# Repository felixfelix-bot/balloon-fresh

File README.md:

# Pico-Balloon Tracker & E80 Range Test Bench

Ultralight (<15 g) pico-balloon tracker (ESP32-C3 + Semtech LR2021) with a
dedicated **E80-STM32 bench firmware** for distributed LoRa/FLRC range
testing.  Two boards, two laptops, one `make` command each — that's all
it takes to run a full PER / RSSI / SNR sweep.

---

## ⚡ Getting Started

```bash
git clone https://github.com/felixfelix-bot/balloon-fresh.git
cd balloon-fresh/firmware/e80-stm32-bench
git checkout feat/2g4-sweep

# One-time: flash the board (needs both USB cables connected)
make flash

# On the TX machine:
make tx

# On the RX machine (within 4 minutes of `make tx`):
make rx

# After both finish, merge logs:
make range-merge RX=rx-log.csv TX=tx-log.csv
```

**That's it.** The system auto-detects serial ports, computes a synchronised
start time (T0), beeps a countdown, and writes results to CSV.

> **Want the minimal package?** Download the pre-built
> [range-test ZIP](../../releases) — contains only the files you need to
> flash + run TX/RX. See [Part 4](#4-minimal-range-test-zip) below.

---

## 📋 Table of Contents

| # | Section |
|---|---------|
| 1 | [What is this repo?](#1-what-is-this-repo) |
| 2 | [Hardware Requirements](#2-hardware-requirements) |
| 3 | [Quick Start (Linux / macOS / Windows)](#3-quick-start) |
| 4 | [Minimal Range-Test ZIP](#4-minimal-range-test-zip) |
| 5 | [Repository Structure](#5-repository-structure) |
| 6 | [Key Documentation](#6-key-documentation) |
| 7 | [Tools Reference](#7-tools-reference) |
| 8 | [Config Presets](#8-config-presets) |
| 9 | [Development & Testing](#9-development--testing) |
| 10 | [Hardware](#10-hardware) |

---

## 1. What is this repo?

This repository hosts **two related projects**:

1. **Pico-Balloon Tracker** — An ESP32-C3 + Semtech LR2021 ultra-light
   balloon tracker (<15 g) with multi-band LoRa (2.4 GHz + Sub-GHz), FLRC
   high-speed mode, 3D PCB-Yagi antenna array, solar/supercap power, and
   BMP280 sensing.

2. **E80 Range Test Bench** — A STM32F103C8T6 based firmware (`firmware/e80-stm32-bench/`)
   for the E80-900MBL-02 board, used for distributed LoRa/FLRC range
   testing.  Measures PER, RSSI, SNR, and bit error rate across modulation
   schemes at various distances.  Two boards act as TX/RX, each connected
   to a separate computer.  Role is set at runtime — boards are
   interchangeable.

---

## 2. Hardware Requirements

| Item | Qty | Notes |
|------|-----|-------|
| E80-900MBL-02 board | 2 | One per machine. Boards are interchangeable (TX/RX is software-selected). |
| Computer (laptop/mini PC) | 2 | One per board. Linux, macOS, or Windows. |
| USB cables | 2 per board | CH340 USB-serial (data) + CMSIS-DAP/Pico SWD probe (debug). Both required. |
| Phone with GPS | 1 (opt.) | For distance measurement. Any app that exports GPX/KML. |

### E80 Board Anatomy

- **STM32F103C8** — microcontroller (64 KB flash / 20 KB RAM)
- **LR2021** — Semtech LoRa Gen 4 radio (supports LoRa + FLRC)
- **CH340** — USB-serial chip for host communication
- **Raspberry Pi Pico** (CMSIS-DAP) — SWD probe for flashing + board reset

### Pico-Balloon Hardware

| Component | Spec |
|-----------|------|
| MCU | ESP32-C3 (ESP-C3-12F / XIAO ESP32C3) |
| LoRa | Semtech LR2021 (Gen 4) / LR1121 (Gen 3 alt.) |
| PA/LNA | Skyworks SKY66112-11 (+22 dBm TX, +14 dB LNA RX) |
| Antennas | 4× PCB-Yagi + SP4T switch (lighthouse mode) |
| Power | 12× solar cells → BAT54 → 2× 3.3 F supercaps → TPS7A02 LDO |
| Sensor | BMP280 (pressure/temperature) |
| Target weight | <15 g |

---

## 3. Quick Start

### Linux

```bash
# Install toolchain
sudo apt install cmake arm-none-eabi-gcc openocd python3 python3-pip
pip install pyserial

# Clone & build
git clone https://github.com/felixfelix-bot/balloon-fresh.git
cd balloon-fresh/firmware/e80-stm32-bench
git checkout feat/2g4-sweep

# Add user to dialout group (needed for serial port access)
sudo usermod -aG dialout "$USER"
# Log out and back in, or: newgrp dialout

# Flash firmware (first time only — both USB cables connected)
make flash
```

### macOS

```bash
# Install toolchain
brew install cmake gcc-arm-embedded openocd python3
pip3 install pyserial

# Clone & build
git clone https://github.com/felixfelix-bot/balloon-fresh.git
cd balloon-fresh/firmware/e80-stm32-bench
git checkout feat/2g4-sweep

make flash
```

### Windows

1. Install [STM32CubeIDE](https://www.st.com/en/development-tools/stm32cubeide.html)
   or a standalone `arm-none-eabi-gcc` toolchain.
2. Install [OpenOCD](https://gnutoolchains.com/arm-eabi/openocd/).
3. Install [Python 3](https://www.python.org/downloads/) + `pip install pyserial`.
4. Clone the repo, open a terminal (Git Bash or PowerShell) in
   `firmware/e80-stm32-bench/`.
5. Run `make flash`.

### Running a Test

```bash
# On TX machine:
make tx

# On RX machine (within 4 minutes of make tx):
make rx

# After both finish (either machine):
make range-merge RX=rx-log.csv TX=tx-log.csv
```

> For full instructions including flashing details, serial port detection,
> GPS stitching, and troubleshooting, see the
> **[E80 Range Test Operator Guide](firmware/e80-stm32-bench/docs/RANGE-TEST-GUIDE.md)**.

---

## 4. Minimal Range-Test ZIP

For operators who just want the files needed to flash + run TX/RX without
cloning the whole repo:

**Download:** See [GitHub Releases](../../releases) for `e80-range-test-*.zip`.

**Build your own:**

```bash
cd firmware/e80-stm32-bench
bash tools/create-range-test-zip.sh
# Output: e80-range-test-<sha7>.zip
```

The ZIP contains:

| Path | Description |
|------|-------------|
| `Makefile` | Convenience targets (flash, tx, rx, merge) |
| `CMakeLists.txt` | Firmware build config |
| `cmake/` | Toolchain file (arm-none-eabi) |
| `ld/` | Linker scripts (STM32F103C8) |
| `src/` | Firmware source code |
| `third_party/` | STM32 HAL + Semtech LR2021 driver |
| `tools/e80_bench_ctl.py` | Board controller — TX/RX, PER bench |
| `tools/e80_detect.py` | Auto-detect board serial port |
| `tools/gps_stitch.py` | Stitch GPS track onto RX packet log |
| `tools/merge_csvs.py` | Merge TX + RX logs into PER report |
| `tools/countdown.py` | Countdown timer with beeps |
| `configs/envelope-4cfg-max.json` | Default range test preset (4 configs, max payload) |
| `configs/outdoor-10.json` | Outdoor range test preset (10 pkts per config) |
| `docs/RANGE-TEST-GUIDE.md` | Full operator guide |
| `README-RANGE-TEST.txt` | Quick start card |

---

## 5. Repository Structure

```
balloon-fresh/
├── firmware/
│   ├── e80-stm32-bench/          # E80 STM32 range test firmware
│   │   ├── Makefile              # Flash, tx, rx, merge targets
│   │   ├── CMakeLists.txt        # Firmware build config
│   │   ├── src/                  # Firmware source (bench, radio, console)
│   │   ├── tools/                # Python tools (comms, GPS, CSV, sweep)
│   │   ├── cmake/                # ARM cross-compile toolchain
│   │   ├── ld/                   # STM32 linker scripts
│   │   ├── third_party/          # STM32 HAL + Semtech LR2021 driver
│   │   ├── docs/                 # RANGE-TEST-GUIDE, flashing, timing analysis
│   │   ├── tests/                # Host-side unit tests (C unit + pytest)
│   │   └── FLASHING.md           # Flashing procedures
│   ├── esp32-c3-flrc/            # ESP32-C3 FLRC bench firmware
│   ├── esp32-bootsel-controller/ # ESP32 boot/select controller
│   ├── esp32-uart-bridge/        # UART bridge firmware
│   ├── rp2040-flrc-max/          # RP2040 FLRC tests
│   └── scripts/                  # Build/deploy scripts
├── mesh-stack/                   # ESP-NOW mesh + FLRC bench + LR2021 drivers
├── hardware/                     # PCB design (KiCad), enclosures
├── configs/                      # Range test config presets (JSON)
├── tools/                        # Shared repo-wide tools & scripts
├── docs/                         # Project documentation, ADRs, plans
├── data/                         # Captured test data & analysis
├── tests/                        # Integration tests
├── bom/                          # Bill of materials
├── ansible/                      # Deployment playbooks (range-setup)
├── scripts/                      # Repo-wide automation scripts
└── tracker/                      # Ground station & tracker firmware
```

---

## 6. Key Documentation

| Document | Description |
|----------|-------------|
| **[Harmonized Cross-Board Bench Package](docs/HARMONIZED-BENCH-PACKAGE.md)** | Entry point for cross-board (E80 / ESP32 / RP2040) bench work — real repo URLs and branches, build/flash per family, running a session, handing data back |
| [Harmonized Results](docs/HARMONIZED-RESULTS.md) | Results summary by board-pair × band × LEN × BR, with raw CSV links; 868 MHz baseline vs 2.4 GHz semantics |
| [Harmonized Run Report Template](docs/HARMONIZED-RUN-REPORT-TEMPLATE.md) | Fill-in template for one harmonized run (identity, provenance, matrix, acceptance, results, anomalies) |
| [Bench Console Spec](docs/BENCH-CONSOLE-SPEC.md) | Normative cross-board console protocol (`ID?/SET/N/PKT/STAT?`, framing, bands) |
| **[E80 Range Test Guide](firmware/e80-stm32-bench/docs/RANGE-TEST-GUIDE.md)** | Complete self-contained operator guide — hardware setup, flashing, TX/RX, merge, GPS, troubleshooting |
| [E80 Flashing Guide](firmware/e80-stm32-bench/FLASHING.md) | Detailed flashing procedures (SWD, stm32flash) |
| [Timing Tolerance Analysis](firmware/e80-stm32-bench/docs/timing-tolerance-analysis.md) | T0 sync mechanism analysis |
| [Hardware Integration Findings](firmware/e80-stm32-bench/docs/hardware-integration-findings.md) | Live hardware test results |
| [Operator Quickstart](firmware/e80-stm32-bench/tools/OPERATOR-QUICKSTART.md) | Quick reference for command structure |
| [ADR Index](docs/adr/) | Architecture Decision Records |
| [Hardware Connections](HARDWARE_CONNECTIONS.md) | Board wiring reference |

---

## 7. Tools Reference

| Tool | Location | Purpose |
|------|----------|---------|
| `e80_bench_ctl.py` | `firmware/e80-stm32-bench/tools/` | Main board controller — TX burst, RX arm, PER measurement, sweep runner |
| `e80_detect.py` | `firmware/e80-stm32-bench/tools/` | Auto-detect E80 board role + serial port (handles CH340 port swapping) |
| `gps_stitch.py` | `firmware/e80-stm32-bench/tools/` | Stitch GPS track points onto RX packet log by nearest timestamp |
| `merge_csvs.py` | `firmware/e80-stm32-bench/tools/` | Merge TX + RX logs into PER report (joins on session/config/pkt_idx) |
| `countdown.py` | `firmware/e80-stm32-bench/tools/` | Countdown to T0 with terminal bell beeps |
| `e80_sweep_full.py` | `firmware/e80-stm32-bench/tools/` | Full modulation sweep (FLRC + LoRa at multiple bitrates/SF) |
| `create-range-test-zip.sh` | `firmware/e80-stm32-bench/tools/` | Build minimal ZIP package for range test operators |

---

## 8. Config Presets

Config files live in `configs/` at the repo root:

| File | Description |
|------|-------------|
| `outdoor-10.json` | Outdoor range test — 10 pkts per config, 868 MHz EU SRD |
| `indoor-baseline.json` | Indoor baseline test |

Each JSON config specifies a list of modulation configurations:

```json
{
  "label": "FLRC-650 LEN64",
  "mod": "flrc",
  "br": 650,
  "pa": 10,
  "freq": 868000000,
  "plen": 64,
  "gap": 5000,
  "n_pkts": 10
}
```

Fields: `mod` (flrc/lora), `sf` (LoRa spreading factor), `bw` (bandwidth kHz),
`br` (bitrate kbps), `pa` (TX power dBm), `freq` (Hz), `plen` (payload bytes),
`gap` (inter-packet gap ms), `n_pkts` (packets per config).

---

## 9. Development & Testing

```bash
# Firmware build
cd firmware/e80-stm32-bench
make firmware          # Cross-compile with arm-none-eabi-gcc

# Host unit tests (uses system gcc)
make test-host

# Run pytest suite
cd firmware/e80-stm32-bench/tools
python3 -m pytest ../tests/ -v

# Run a dry-run of the range test (prints schedule, no hardware)
make range-dry-run
```

---

## 10. Hardware

| Directory | Description |
|-----------|-------------|
| `hardware/` | PCB design files (KiCad), enclosure CAD |
| `bom/` | Bill of materials |
| `docs/pcb/` | PCB design documentation |
| `docs/hardware-reference/` | Hardware reference materials |

---

## License

See individual source files and `firmware/e80-stm32-bench/third_party/`
for licensing details. Third-party drivers retain their original licenses
(Semtech BSD, ST BSD-3-Clause).

## Cross-Board Bench — dieser Branch (`range-tests`)
Dieser Branch ist die Range-Test-Spur der harmonisierten Cross-Board-Messungen
(E80 STM32+LR2021 / ESP32-C3+LR2021 / RP2040+LR2021). Einstiegspunkt für alles
Weitere ist `docs/HARMONIZED-BENCH-PACKAGE.md` im Branch **`main`** desselben
Repos (`https://github.com/felixfelix-bot/balloon-fresh.git`).
> **Wichtig — die Bench-Console liegt NICHT auf diesem Branch.**
> `tools/balloon_sweep.py` und `docs/BENCH-CONSOLE-SPEC.md` gibt es nur auf
> `main` (HARM-Kette, `harm/t5-bench-console`). Auf `range-tests` schlägt
> `ls tools/balloon_sweep.py` fehl. Wer die harmonisierte Console fahren will,
> muss `main` auschecken oder diesen Branch damit mergen; die untenstehenden
> Kommandos sind die *Legacy*-Sweep-Werkzeuge dieses Branches.
### RP2040-Firmware bauen/flashen (dieser Branch)
cd firmware/rp2040
make build-tx        # bzw. build-rx / build-both
make flash-tx        # bzw. flash-rx / flash-both
make monitor-tx      # bzw. monitor-rx
make ports           # Ports neu ermitteln (nicht raten)
### Sweep fahren (Legacy-Weg dieses Branches)
# Board-Mutex ist Pflicht — niemals ohne Lock flashen
BALLOON_TRACK=range-tests python3 ~/repos/balloon-fresh/tools/balloon-board-lock.py \
    acquire board-a --purpose "range sweep" --timeout 120
python3 tools/sweep_flash.py          # flashen
python3 tools/sweep_capture.py 480    # 480 s erfassen (>= 2 Zyklen)
python3 tools/capture_sweep.py        # alternativ: Sweep-Capture
BALLOON_TRACK=range-tests python3 ~/repos/balloon-fresh/tools/balloon-board-lock.py release board-a
Die Ergebnisse und die bekannten Fallstricke dieses Ansatzes (Timing-Drift
zwischen zwei freilaufenden RP2040, Slot-Weiten, IRQ-/RSSI-Opcode-Bugs) stehen in
`docs/SWEEP-RESULTS.md`. Datenübergabe-Konvention dieses Branches:
`docs/data-handover/DATA-HANDOVER-2026-08-17.md`.
### Harmonisierte Session (nur auf `main`)
git checkout main     # Console liegt dort
python3 tools/balloon_sweep.py --tx rp2040 --rx esp32 --session <yymmddHHMM> --dry-run
`REFUSED (pre-hardware, spec enforcement): …` heisst: der Plan verletzt die Spec
(LEN-Cap 255/511, GAP >= 40 000 us bei LEN > 256, Frequenz-Paar). Plan
korrigieren, nicht umgehen. 2.4-GHz-Cross-Board ist nur RP2040<->ESP32 erlaubt.

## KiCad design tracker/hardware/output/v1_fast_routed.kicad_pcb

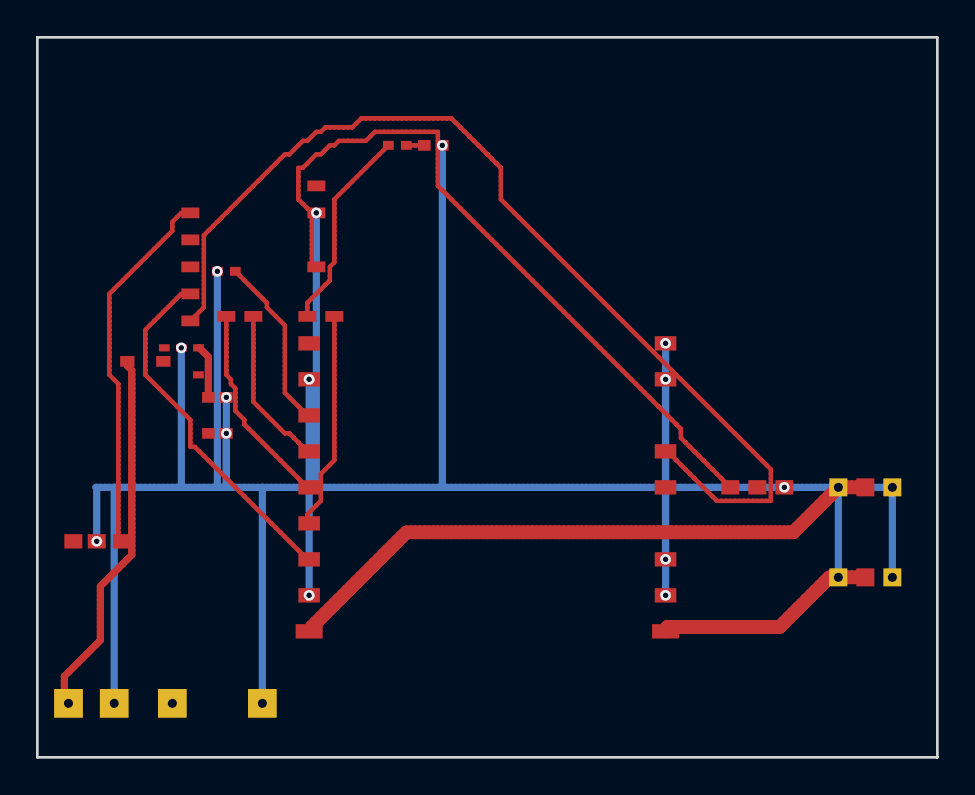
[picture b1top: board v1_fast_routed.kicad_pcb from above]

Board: 2 copper layers, 50.0 x 40.0 mm, 15 parts (0 on the bottom side), 17 nets.

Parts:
ANT1: U.FL-868
ANT2: U.FL-2400
C1, C2: 10uF
C_CAP: Supercap
D1: BAT54
FEM: FEM
LED1: LED-0603
R_LED: 330R
R_PD: 10k
SOLAR: Solar-Conn
U1: ESP32-C3
U2: LR2021F33
U3: MAX-M10S
U4: TPS7A02

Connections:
3V3: C2.1, FEM.VCC, U1.VCC, U2.1, U3.1, U4.4
FEM_TX: FEM.TX, U1.GPIO19
GND: ANT1.2, ANT1.3, ANT2.2, ANT2.3, C1.2, C2.2, C_CAP.2, FEM.GND, LED1.K, R_PD.1, SOLAR.2, U1.GND, U2.2, U2.8, U2.10, U2.11, U2.16, U2.17, U3.2, U4.2
GPS_RX: U1.GPIO1, U3.3
LED_ANODE: LED1.A, R_LED.2
LR2021_BUSY: U1.GPIO4, U2.7
LR2021_DIO9: U1.GPIO5, U2.13
LR2021_RST: U1.GPIO3, U2.14
RF_2G4_2400: ANT2.1, U2.18
RF_SUB_868: ANT1.1, U2.9
SOLAR_IN: D1.A, SOLAR.1
SPI_MISO: R_PD.2, U1.GPIO2, U2.3
SPI_MOSI: U1.GPIO7, U2.4
SPI_NSS: U1.GPIO10, U2.6
SPI_SCK: U1.GPIO6, U2.5
STATUS_LED: R_LED.1, U1.GPIO9
VCAP: C1.1, C_CAP.1, D1.K, U4.1, U4.3

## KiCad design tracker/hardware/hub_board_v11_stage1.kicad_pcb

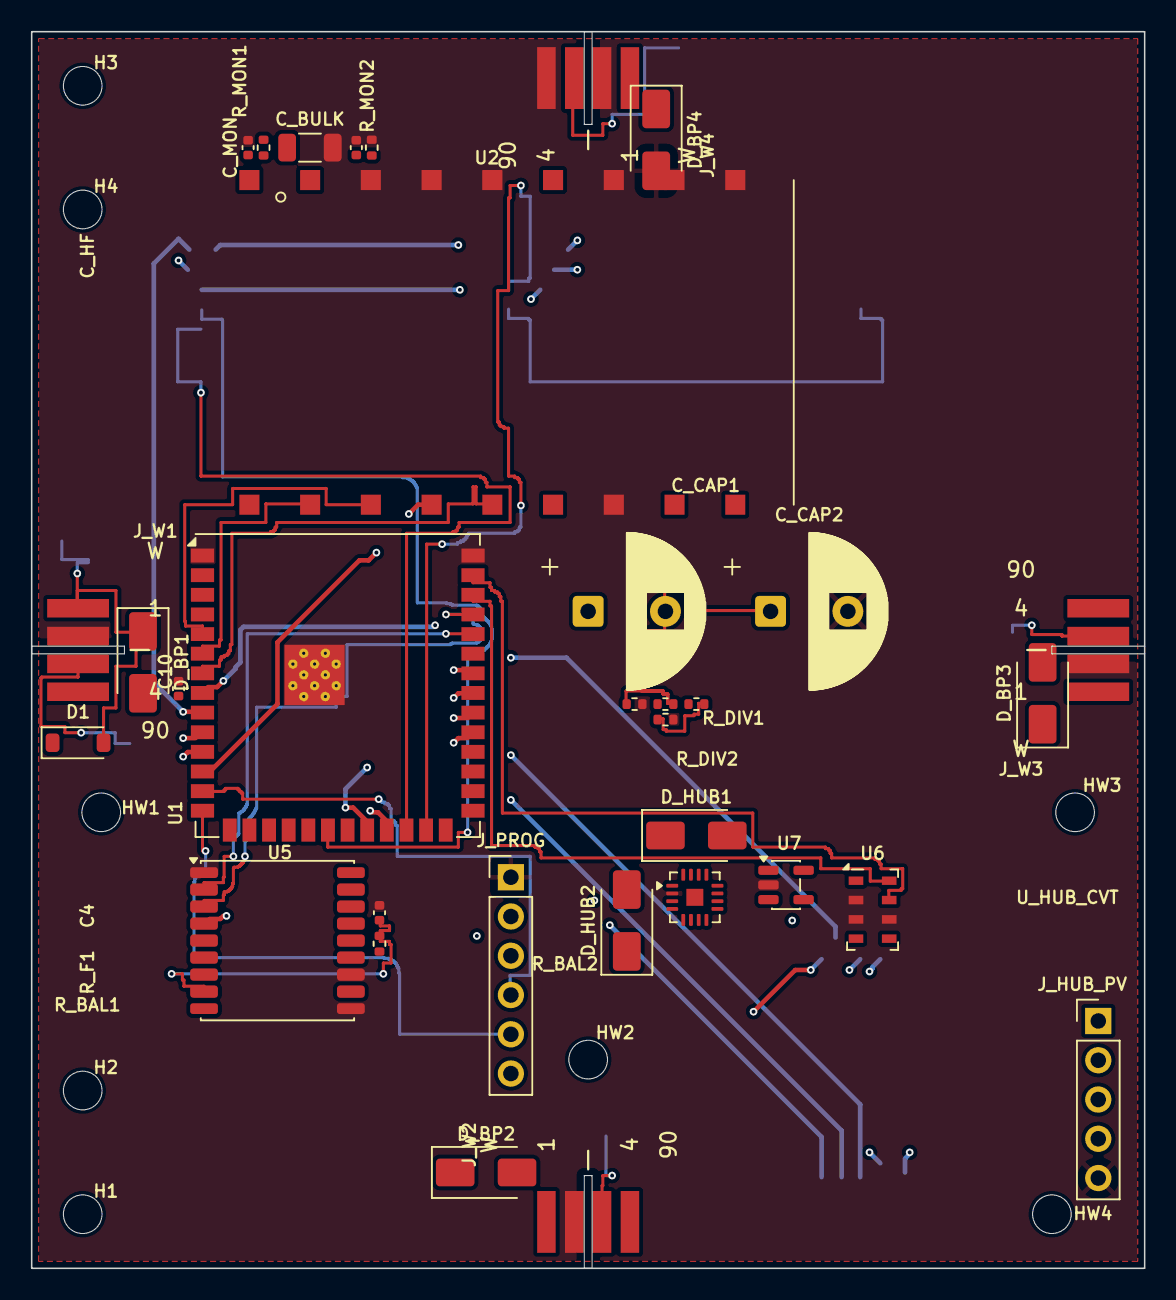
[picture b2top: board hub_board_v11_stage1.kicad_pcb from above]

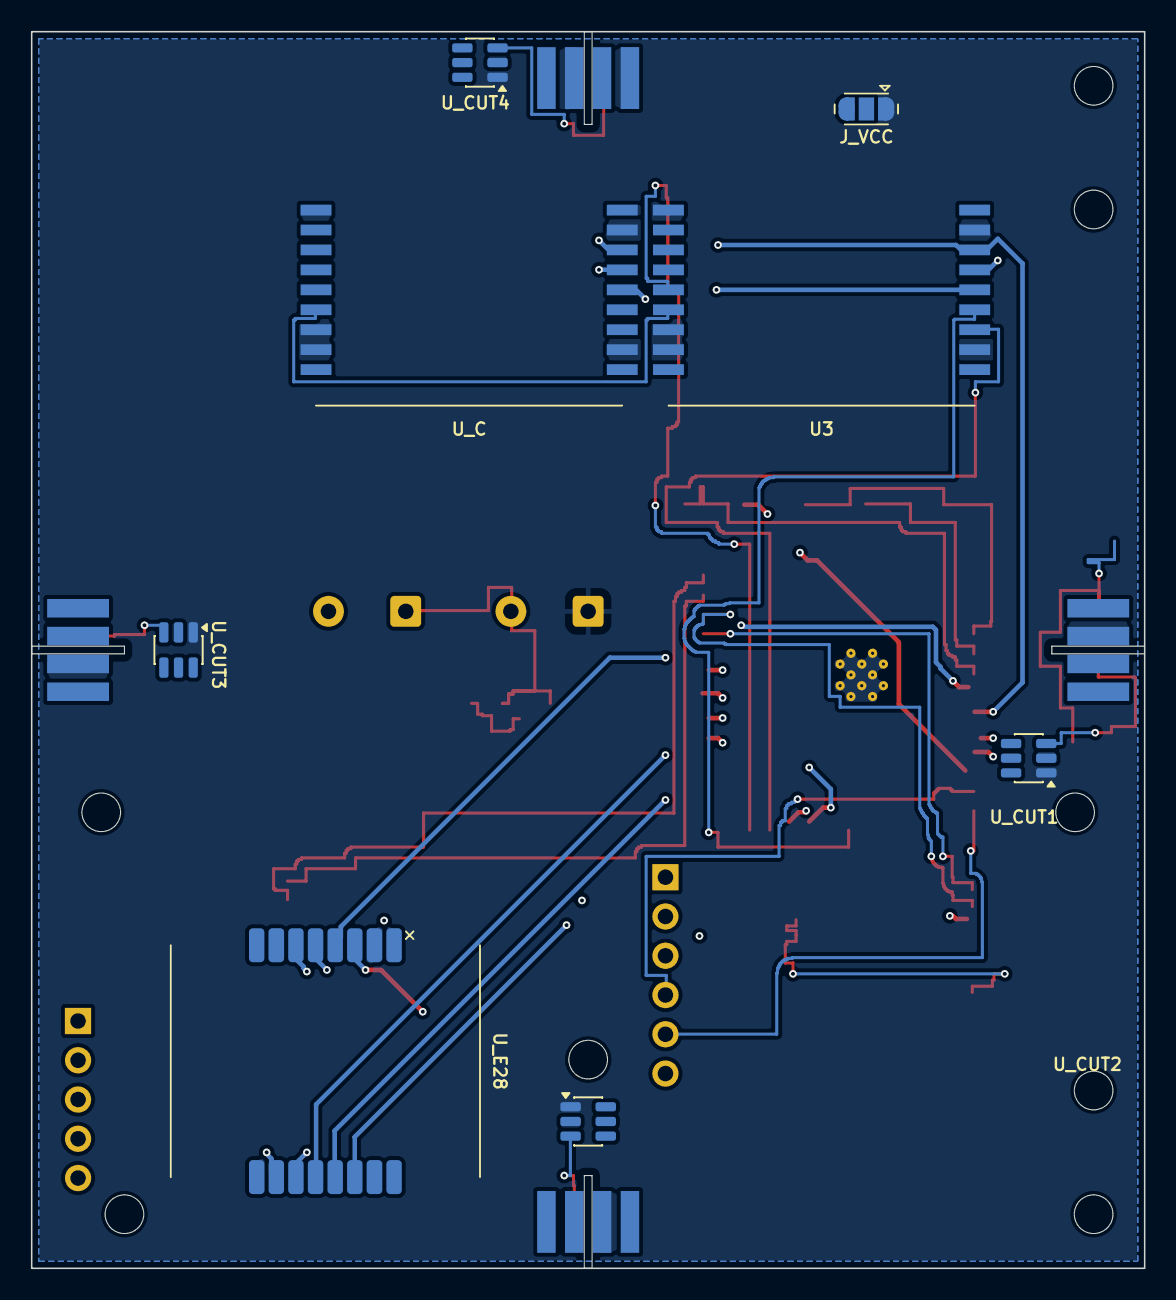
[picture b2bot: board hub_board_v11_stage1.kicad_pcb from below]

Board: 4 copper layers, 72.0 x 80.0 mm, 49 parts (8 on the bottom side), 48 nets.

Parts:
C4, C10: 10uF; C_0402_1005Metric
C_BULK: 100uF; C_1206_3216Metric
C_CAP1: C_CAP1; CP_Radial_D10.0mm_P5.00mm
C_CAP2: C_CAP2; CP_Radial_D10.0mm_P5.00mm
C_HF: 100nF; C_0402_1005Metric
C_MON: 10nF; C_0402_1005Metric
D1: BAT54; D_SOD-123
D_BP1, D_BP2, D_BP3, D_BP4: SS24; D_SMA
D_HUB1, D_HUB2: SS24; D_SMA
H1, H2, H3, H4: TETHER_NPTH_D2.5; MountingHole_2.5mm
HW1, HW2, HW3, HW4: STRING_NPTH_D2.5; MountingHole_2.5mm
J_HUB_PV: HUB_PV_PANEL_5P (P | MID1 | spare | N | GND); PinHeader_1x05_P2.54mm_Vertical
J_PROG: J_PROG; PinHeader_1x06_P2.54mm_Vertical
J_VCC: F33_VCC_SEL (VSCAP | +3V3); SolderJumper-3_P1.3mm_Open_RoundedPad1.0x1.5mm
J_W1, J_W2, J_W3, J_W4: WING_SOCKET_4P; Wing_Tab_4P
R_BAL1, R_BAL2: 10k; R_0402_1005Metric
R_DIV1, R_DIV2: 1M; R_0402_1005Metric
R_F1: 100R; R_0402_1005Metric
R_MON1, R_MON2: 4.7M; R_0402_1005Metric
U1: U1; ESP32-S3-WROOM-1U
U2: U2; LoRa2021F33_2G4
U3: U3; LoRa2021_Castellated
U5: U5; ublox_MAX
U6: U6; LGA-8_3x5mm_P1.25mm
U7: U7; SOT-23-5
U_C: U_C; LoRa2021_Castellated
U_CUT1, U_CUT2, U_CUT3, U_CUT4: latched cut driver + cut-sense (part TODO(unverif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; SOT-23-6
U_E28: U_E28; E28-2G4M27SX
U_HUB_CVT: U_HUB_CVT; VQFN-16-1EP_3x3mm_P0.5mm_EP1.1x1.1mm

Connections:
+3V3: C10.1, J_PROG.2, J_VCC.3, R_F1.1, U1.2, U2.5, U3.1, U5.6, U5.7, U5.9, U6.1, U6.4, U6.5, U7.5, U_C.1, U_E28.1
/CUT_SENSE_W1: J_W1.3, U_CUT1.3
/CUT_SENSE_W2: J_W2.3, U_CUT2.3
/CUT_SENSE_W3: J_W3.3, U_CUT3.3
/CUT_SENSE_W4: J_W4.3, U_CUT4.3
/E28_BUSY: U1.31, U_E28.12
/E28_CS_N: U1.10, U_E28.6
/E28_DIO1: U1.33, U_E28.13
/E28_DIO2: U1.11, U_E28.14
/E28_DIO3: U1.34, U_E28.15
/E28_RESET_N: U1.32, U_E28.11
/EN: J_PROG.3, U1.3
/F33_BUSY: U1.12, U2.14
/F33_CS_N: U1.7, U2.13
/F33_IRQ: U1.17, U2.18
/F33_RESET_N: U1.18, U2.17
/F33_VCC: C_BULK.1, C_HF.1, J_VCC.2, R_MON1.1, U2.1
/F33_VSENSE: C_MON.1, R_MON1.2, R_MON2.1, U1.21
/GNSS_PPS: U1.23, U5.4
/GNSS_RX: U1.37, U5.3
/GNSS_TX: U1.36, U5.2
/GNSS_VCC: C4.1, R_F1.2, U5.8
/HUB_PV_MID1: D_HUB1.2, D_HUB2.1, J_HUB_PV.2
/HUB_PV_N: D_HUB2.2, J_HUB_PV.4, U_HUB_CVT.3
/HUB_PV_P: D_HUB1.1, J_HUB_PV.1, U_HUB_CVT.1
/I2C_SCL: U1.38, U6.8
/I2C_SDA: U1.39, U6.7
/SCAP_ADC: R_DIV1.2, R_DIV2.1
/SCAP_MID: C_CAP1.2, C_CAP2.1, R_BAL1.2, R_BAL2.1
/SPI1_MISO: U1.9, U3.3, U_C.3, U_E28.3
/SPI1_MOSI: U1.8, U3.4, U_C.4, U_E28.4
/SPI1_SCK: U1.22, U3.5, U_C.5, U_E28.5
/SPI2_MISO: U1.6, U2.16
/SPI2_MOSI: U1.5, U2.15
/SPI2_SCK: U1.4, U2.12
/U3_BUSY: U1.24, U3.7
/U3_CS_N: U1.20, U3.6
/U3_IRQ: U1.19, U3.15
/U3_RESET_N: U1.25, U3.14
/USB_DN: J_PROG.4, U1.13
/USB_DP: J_PROG.5, U1.14
/VSCAP: C_CAP1.1, D1.1, J_VCC.1, R_BAL1.1, R_DIV1.1, U7.1, U7.3, U_CUT1.1, U_CUT2.1, U_CUT3.1, U_CUT4.1
/VTCXO_VNTC: U3.13, U_C.13
/W1_SOLAR_N: D_BP1.2, D_BP2.1, J_W1.4, J_W2.1
/W1_SOLAR_P: D1.2, D_BP1.1, J_W1.1
/W2_SOLAR_N: D_BP2.2, D_BP3.1, J_W2.4, J_W3.1
/W3_SOLAR_N: D_BP3.2, D_BP4.1, J_W3.4, J_W4.1
GND: C4.2, C10.2, C_BULK.2, C_CAP2.2, C_HF.2, C_MON.2, D_BP4.2, J_HUB_PV.5, J_PROG.1, J_W1.2, J_W2.2, J_W3.2, J_W4.2, J_W4.4, R_BAL2.2, R_DIV2.2, R_MON2.2, U1.1, U1.40, U1.41, U2.2, U2.3, U2.4, U2.6, U2.7, U2.8, U2.11, U3.2, U3.8, U3.11, U3.12, U3.18, U5.1, U5.10, U5.12, U6.2, U6.3, U6.6, U7.2, U_C.2, U_C.8, U_C.11, U_C.12, U_C.18, U_CUT1.2, U_CUT2.2, U_CUT3.2, U_CUT4.2, U_E28.2, U_E28.7, U_E28.10, U_E28.16, U_HUB_CVT.2

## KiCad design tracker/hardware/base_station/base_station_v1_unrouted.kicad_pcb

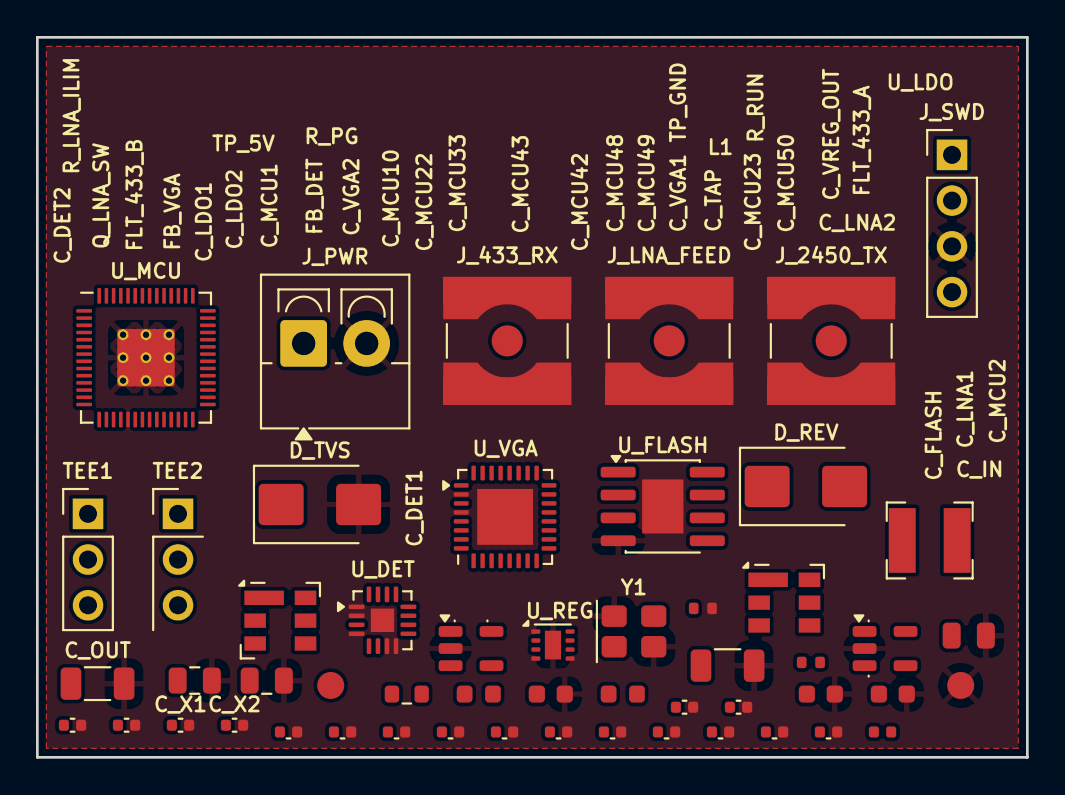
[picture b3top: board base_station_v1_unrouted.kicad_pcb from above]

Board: 4 copper layers, 55.0 x 40.0 mm, 53 parts (0 on the bottom side), 33 nets, no tracks yet.

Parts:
C_DET1: 100nF; C_0402_1005Metric
C_DET2: 100nF (VOUT filter); C_0402_1005Metric
C_FLASH: 100nF X7R flash bypass; C_0402_1005Metric
C_IN: GRM31CR61E106KA12L 10uF 25V X5R 10%; C_1206_3216Metric
C_LDO1, C_LDO2: 2.2uF 16V X7R 10% (effective >=1uF required); C_0805_2012Metric
C_LNA1: 100nF (tee DC injection bypass); C_0402_1005Metric
C_LNA2: 10uF (tee DC injection bypass); C_0805_2012Metric
C_MCU1: 100nF; C_0402_1005Metric
C_MCU2: 1uF; C_0603_1608Metric
C_MCU10: 100nF X7R MCU pad10; C_0402_1005Metric
C_MCU22: 100nF X7R MCU pad22; C_0402_1005Metric
C_MCU23: 100nF X7R MCU pad23; C_0402_1005Metric
C_MCU33: 100nF X7R MCU pad33; C_0402_1005Metric
C_MCU42: 100nF X7R MCU pad42; C_0402_1005Metric
C_MCU43: 100nF X7R MCU pad43; C_0402_1005Metric
C_MCU48: 100nF X7R MCU pad48; C_0402_1005Metric
C_MCU49: 100nF X7R MCU pad49; C_0402_1005Metric
C_MCU50: 100nF X7R MCU pad50; C_0402_1005Metric
C_OUT: GRM31CR71A226KE15L 22uF 10V X7R 10%; C_1206_3216Metric
C_TAP: directional/coupled tap after the BPF/LNA (TODO(u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; C_0402_1005Metric
C_VGA1: 100nF; C_0402_1005Metric
C_VGA2: 1uF; C_0603_1608Metric
C_VREG_OUT: 1uF X7R VREG_OUT pad45; C_0603_1608Metric
C_X1, C_X2: 15pF; C_0402_1005Metric
D_REV: reverse-polarity/TVS protection; D_SMB
D_TVS: TVS clamp (set point TODO(unverified)); D_SMB
FB_DET: ferrite bead; L_0603_1608Metric
FB_VGA: ferrite bead / pi filter; L_0603_1608Metric
FLT_433_A: 433 MHz BPF (ahead of LNA); Filter_SAW-6_3.8x3.8mm
FLT_433_B: 433 MHz BPF #2 (before the AD8318 -- mandatory); Filter_SAW-6_3.8x3.8mm
J_433_RX: 433 MHz RX antenna port (SMA); SMA_Amphenol_132134-10_Vertical
J_2450_TX: 2.45 GHz TX antenna port (SMA; no PA on the PCBA); SMA_Amphenol_132134-10_Vertical
J_LNA_FEED: coax feed to the masthead LNA (SMA); SMA_Amphenol_132134-10_Vertical
J_PWR: VIN_GS 9-18V input; TerminalBlock_4Ucon_1x02_P3.50mm_Vertical
J_SWD: SWD debug header 1x4; PinHeader_1x04_P2.54mm_Vertical
L1: SRN4018-2R2M 2.2uH 20% 2.9A Irms 3.0A Isat; L_Bourns-SRN4018
Q_LNA_SW: load switch / resettable limiter (ADL5240 must NO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; SOT-23-5
R_LNA_ILIM: set LNA branch current limit; R_0402_1005Metric
R_PG: RC0603FR-07100KL 100k 1% PG pull-up; R_0603_1608Metric
R_RUN: 10k RUN pull-up; R_0402_1005Metric
TEE1: Mini-Circuits ZFBT-4R2GW+ bias tee (masthead feed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; PinHeader_1x03_P2.54mm_Vertical
TEE2: ZFBT-4R2GW+ bias tee (board side); PinHeader_1x03_P2.54mm_Vertical
TP_5V: +5V_PCBA test point; TestPoint_Pad_D1.5mm
TP_GND: GND test point; TestPoint_Pad_D1.5mm
U_DET: AD8318ACPZ-R7 log detector (68mA typ, 82mA max at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; LFCSP-16-1EP_3x3mm_P0.5mm_EP1.3x1.3mm
U_FLASH: QSPI flash (RP2040 boot); SOIC-8-1EP_3.9x4.9mm_P1.27mm_EP2.29x3mm
U_LDO: AP2112K-3.3TRG1 fixed 3.3V; SOT-23-5
U_MCU: RP2040 QFN-56; RP2040-QFN-56
U_REG: TPS62163DSGR fixed 5V buck (3-17V in, 1A out); WSON-8-1EP_2x2mm_P0.5mm_EP0.9x1.6mm
U_VGA: ADL5240 VGA (93mA @ 4.75-5.25V, gain from RP2040); LFCSP-32-1EP_5x5mm_P0.5mm_EP3.1x3.1mm
Y1: 12MHz crystal; Crystal_SMD_3225-4Pin_3.2x2.5mm

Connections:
+1V1_CORE: C_MCU23.1, C_MCU50.1, C_VREG_OUT.1, U_MCU.23, U_MCU.45, U_MCU.50
+3V3_MCU: C_FLASH.1, C_LDO1.1, C_MCU1.1, C_MCU2.1, C_MCU10.1, C_MCU22.1, C_MCU33.1, C_MCU42.1, C_MCU43.1, C_MCU48.1, C_MCU49.1, J_SWD.1, R_PG.1, R_RUN.1, U_FLASH.8, U_LDO.5, U_MCU.1, U_MCU.10, U_MCU.22, U_MCU.33, U_MCU.42, U_MCU.43, U_MCU.44, U_MCU.48, U_MCU.49
+5V_DET: C_DET1.1, FB_DET.2, U_DET.5
+5V_LNA_SW: C_LNA1.1, C_LNA2.1, Q_LNA_SW.5, TEE1.3, TEE2.3
+5V_PCBA: C_LDO2.1, C_OUT.1, FB_DET.1, FB_VGA.1, L1.2, Q_LNA_SW.1, TP_5V.1, U_LDO.1, U_LDO.3, U_REG.6
+5V_VGA: C_VGA1.1, C_VGA2.1, FB_VGA.2, U_VGA.1
DET_RF_IN: FLT_433_B.2, U_DET.3
DET_VOUT: C_DET2.1, U_DET.6, U_MCU.38
GND: C_DET1.2, C_DET2.2, C_FLASH.2, C_IN.2, C_LDO1.2, C_LDO2.2, C_LNA1.2, C_LNA2.2, C_MCU1.2, C_MCU2.2, C_MCU10.2, C_MCU22.2, C_MCU23.2, C_MCU33.2, C_MCU42.2, C_MCU43.2, C_MCU48.2, C_MCU49.2, C_MCU50.2, C_OUT.2, C_VGA1.2, C_VGA2.2, C_VREG_OUT.2, C_X1.2, C_X2.2, D_TVS.2, J_433_RX.2, J_2450_TX.2, J_LNA_FEED.2, J_PWR.2, J_SWD.3, Q_LNA_SW.2, R_LNA_ILIM.2, TP_GND.1, U_DET.1, U_DET.2, U_DET.4, U_DET.7, U_DET.8, U_DET.17, U_FLASH.4, U_FLASH.9, U_LDO.2, U_MCU.19, U_MCU.57, U_REG.1, U_REG.4, U_REG.5, U_REG.9, U_VGA.2, U_VGA.4, U_VGA.33, Y1.2, Y1.4
LNA_EN: Q_LNA_SW.3, U_MCU.32
LNA_FLT: Q_LNA_SW.4, R_LNA_ILIM.1, U_MCU.34
QSPI_SCLK: U_FLASH.6, U_MCU.52
QSPI_SD0: U_FLASH.5, U_MCU.53
QSPI_SD1: U_FLASH.2, U_MCU.55
QSPI_SD2: U_FLASH.3, U_MCU.54
QSPI_SD3: U_FLASH.7, U_MCU.51
QSPI_SS: U_FLASH.1, U_MCU.56
REG_PG: R_PG.2, U_MCU.37, U_REG.8
REG_SW: L1.1, U_REG.7
RF_433_ANT: FLT_433_A.1, J_433_RX.1
RF_433_BPF1: FLT_433_A.2, TEE1.1
RF_TAP: C_TAP.2, FLT_433_B.1
RUN: R_RUN.2, U_MCU.26
SWCLK: J_SWD.4, U_MCU.24
SWDIO: J_SWD.2, U_MCU.25
VGA_GAIN0: U_MCU.29, U_VGA.6
VGA_GAIN1: U_MCU.30, U_VGA.7
VGA_GAIN2: U_MCU.31, U_VGA.8
VGA_RF_IN: C_TAP.1, TEE2.2, U_VGA.3
VIN_GS: D_REV.2, J_PWR.1
VIN_GS_PROT: C_IN.1, D_REV.1, D_TVS.1, U_REG.2, U_REG.3
XIN: C_X1.1, U_MCU.20, Y1.1
XOUT: C_X2.1, U_MCU.21, Y1.3

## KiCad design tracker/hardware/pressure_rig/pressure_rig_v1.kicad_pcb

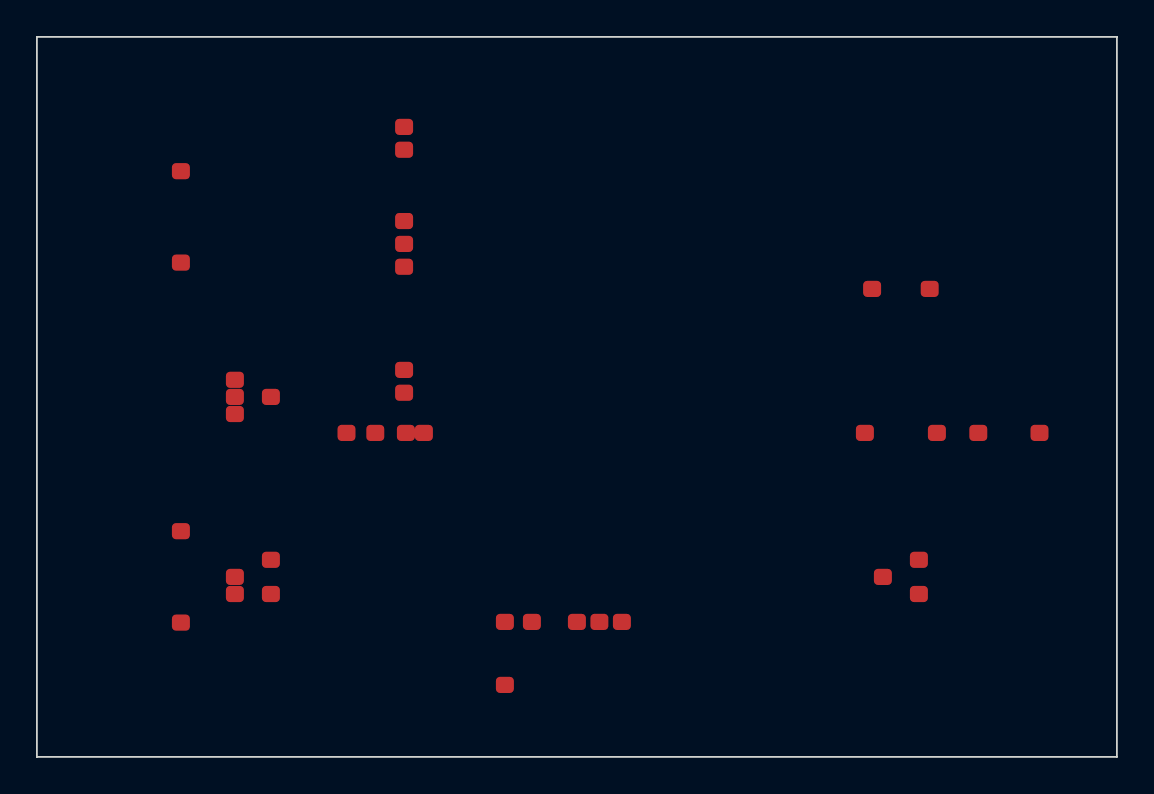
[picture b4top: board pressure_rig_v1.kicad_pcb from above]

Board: 2 copper layers, 60.0 x 40.0 mm, 12 parts (0 on the bottom side), 10 nets, no tracks yet.

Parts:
C1: 10uF; C_0603_1608Metric
C2: 100nF; C_0402_1005Metric
C3: 100uF; C_1206_3216Metric
D1: SS24; D_SMA
D2: BAT54; D_SOD-123
J1: USB_C; USB_C_Receptacle_USB2.0
J2: PUMP; TerminalBlock_1x02_P5.08mm
J3: 12V_IN; TerminalBlock_1x02_P5.08mm
Q1: IRLML6344; SOT-23
U1: ESP32-S3-WROOM-1U
U2: BMP280; LGA-8_BMP280
U3: TPS7A0233; SOT-23-5

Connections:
+3V3: C1.1, C2.1, U1.3, U2.8, U3.5
+5V: D2.2, J1.A4, J1.B9, U3.1, U3.3
GND: C1.2, C2.2, C3.2, J1.A1, J1.B1, J3.2, Q1.3, U1.2, U2.1, U3.2
I2C_SCL: U1.9, U2.4
I2C_SDA: U1.8, U2.6
PUMP_EN: Q1.1, U1.4
PUMP_SW: D1.1, J2.1, Q1.2
USB_DN: J1.A7, U1.19
USB_DP: J1.A6, U1.20
VIN_12V: C3.1, D1.2, D2.1, J2.2, J3.1

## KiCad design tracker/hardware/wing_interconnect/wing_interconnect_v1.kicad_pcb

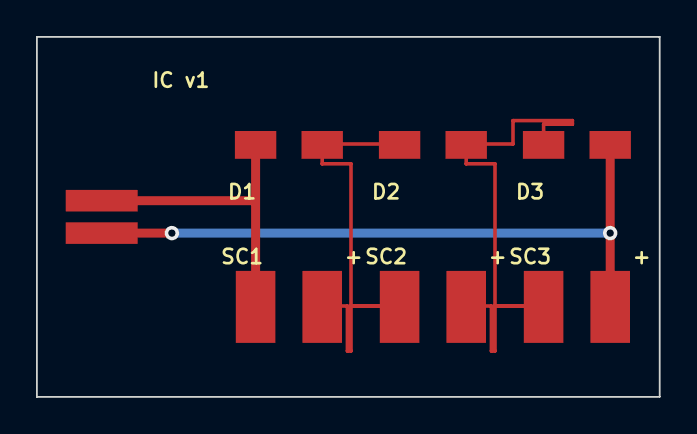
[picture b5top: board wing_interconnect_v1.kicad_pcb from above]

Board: 2 copper layers, 34.6 x 20.0 mm, 7 parts (0 on the bottom side), 4 nets.

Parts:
D1, D2, D3: D_SMA_Wing
J1: Tab_2P
SC1, SC2, SC3: SolarTail_2P

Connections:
SOLAR_MID1: D1.2, D2.1, SC1.2, SC2.1
SOLAR_MID2: D2.2, D3.1, SC2.2, SC3.1
SOLAR_N: D3.2, J1.2, SC3.2
SOLAR_P: D1.1, J1.1, SC1.1

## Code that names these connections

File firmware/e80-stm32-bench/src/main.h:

/**
 * @file    main.h
 * @brief   E80 (LR2021 module, STM32F103C8T6 host) bench firmware - common defs.
 *
 * Pin map copied verbatim from the vendor E80_DEMO CubeMX project
 * (E80/Core/Inc/main.h) so the vendored radio_hal/lr20xx_hal.c builds
 * unmodified against this header:
 *
 *   PA3  E80_BUSY   (input, radio BUSY)
 *   PA4  RADIO_NSS  (soft NSS, push-pull)
 *   PA5  SPI1_SCK   PA6 SPI1_MISO   PA7 SPI1_MOSI  (~9 MHz: 72/8)
 *   PB0  E80_NRST   (radio hardware reset)
 *   PB1  E80_DIO9   (EXTI1, unused by bench - demo wires it as well)
 *   PB2  E80_DIO8   (EXTI2, radio IRQ pin per demo DIO8-as-IRQ)
 *   PB12 LED2  PB13 LED1 (active low)
 *   PB14 KEY2  PB15 KEY1 (plain GPIO user keys, pull-up)
 */

#ifndef E80_MAIN_H
#define E80_MAIN_H

#ifdef __cplusplus
extern "C" {
#endif

#include "stm32f1xx_hal.h"

/* ---- Radio / board pin defines (names used by third_party radio_hal) ------- */
#define E80_BUSY_Pin       GPIO_PIN_3
#define E80_BUSY_GPIO_Port GPIOA

#define RADIO_NSS_Pin       GPIO_PIN_4
#define RADIO_NSS_GPIO_Port GPIOA

#define E80_NRST_Pin       GPIO_PIN_0
#define E80_NRST_GPIO_Port GPIOB

#define E80_DIO9_Pin       GPIO_PIN_1
#define E80_DIO9_GPIO_Port GPIOB
#define E80_DIO9_EXTI_IRQn EXTI1_IRQn

#define E80_DIO8_Pin       GPIO_PIN_2
#define E80_DIO8_GPIO_Port GPIOB
#define E80_DIO8_EXTI_IRQn EXTI2_IRQn

#define LED2_Pin       GPIO_PIN_12
#define LED2_GPIO_Port GPIOB
#define LED1_Pin       GPIO_PIN_13
#define LED1_GPIO_Port GPIOB

#define KEY2_Pin       GPIO_PIN_14
#define KEY2_GPIO_Port GPIOB
#define KEY1_Pin       GPIO_PIN_15
#define KEY1_GPIO_Port GPIOB

/* ---- Bench app configuration ---------------------------------------------- */

/* Safety: compile-time default state = radio asleep, TX inhibited.
 * TX requires the two-step ROLE TX + ARM TX command sequence at runtime. */
#define E80_BENCH_BOOT_TX_INHIBITED 1

/* Default console: USART1 2,000,000 8N1. CH340 supports 2 Mbps,
 * STM32F103 USART1 supports up to 4.5 Mbps. The RX path is
 * interrupt-driven with a ring buffer. */
#define E80_BENCH_BAUD_DEFAULT 115200U

/* Radio default: 868.0 MHz (EU SRD 863-870). */
#define E80_BENCH_FREQ_DEFAULT_HZ 868000000UL

/* EU SRD band clamp (safety gate): FREQ only accepts 863-870 MHz unless the
 * operator explicitly runs BAND OVERRIDE <pin>. 900 MHz is NOT license-exempt
 * in the EU — the override exists for lab exceptions only. */
#define E80_BENCH_BAND_MIN_HZ 863000000UL
#define E80_BENCH_BAND_MAX_HZ 870000000UL
#define E80_BENCH_OVERRIDE_PIN 2026
/* With override: full LR2021 range (dual-band: sub-GHz LF + 2.4 GHz HF path).
 * Felix confirmed E80 boards have dual radios with separate antennas. */
#define E80_BENCH_OVERRIDE_MIN_HZ 410000000UL
#define E80_BENCH_OVERRIDE_MAX_HZ 2483500000UL

/* 2.4 GHz ISM band (HF path, PA_SEL_HF + RX_PATH_HF). */
#define E80_BENCH_BAND_2G4_MIN_HZ 2400000000UL
#define E80_BENCH_BAND_2G4_MAX_HZ 2483500000UL

/* Indoor TX power cap (safety gate, Felix Aug 16): default max +10 dBm on the
 * desk bench. +22 dBm only after explicit 'POWER MODE OUTDOOR 2026' unlock. */
#define E80_BENCH_TXPOW_CAP_INDOOR_DBM 10
#define E80_BENCH_TXPOW_MAX_DBM 22

/* Max FLRC payload 511 B (LoRa caps at 255). Buffers sized to the max. */
#define E80_BENCH_MAX_PAYLOAD 512

#ifdef __cplusplus
}
#endif

#endif /* E80_MAIN_H */

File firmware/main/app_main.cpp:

#include <stdio.h>
#include <string.h>
#include "freertos/FreeRTOS.h"
#include "freertos/task.h"
#include "esp_log.h"
#include "esp_pm.h"
#include "driver/gpio.h"

#include <RadioLib.h>
#include "EspHalC3.h"

extern "C" {
#include "bmp280.h"
#include "power_manager.h"
#include "telemetry.h"
#include "antenna_switch.h"
}

static const char *TAG = "MAIN";

#define LED_GPIO 10

#define LR2021_SCK   6
#define LR2021_MISO  2
#define LR2021_MOSI  7
#define LR2021_NSS   10
#define LR2021_BUSY  4
#define LR2021_RST   3
#define LR2021_DIO9  5

static EspHalC3* hal = nullptr;
static LR2021* radio = nullptr;

static bool flag_tx_done = false;

static void on_tx_done(void) {
    flag_tx_done = true;
}

static void blink_led(int times)
{
    gpio_config_t io_conf = {
        .pin_bit_mask = (1ULL << LED_GPIO),
        .mode = GPIO_MODE_OUTPUT,
        .pull_up_en = GPIO_PULLUP_DISABLE,
        .pull_down_en = GPIO_PULLDOWN_DISABLE,
        .intr_type = GPIO_INTR_DISABLE,
    };
    gpio_config(&io_conf);

    for (int i = 0; i < times; i++) {
        gpio_set_level((gpio_num_t)LED_GPIO, 1);
        vTaskDelay(pdMS_TO_TICKS(100));
        gpio_set_level((gpio_num_t)LED_GPIO, 0);
        vTaskDelay(pdMS_TO_TICKS(100));
    }
}

extern "C" void app_main(void)
{
    ESP_LOGI(TAG, "Pico Balloon Tracker v0.1 starting...");

    esp_pm_config_t pm_config = {
        .max_freq_mhz = 80,
        .min_freq_mhz = 10,
        .light_sleep_enable = true,
    };
    ESP_ERROR_CHECK(esp_pm_configure(&pm_config));

    blink_led(3);

    hal = new EspHalC3(LR2021_SCK, LR2021_MISO, LR2021_MOSI);

    radio = new LR2021(new Module(hal, LR2021_NSS, LR2021_DIO9, LR2021_RST, LR2021_BUSY));
    radio->irqDioNum = 9;

    ESP_LOGI(TAG, "Initializing LR2021 (RadioLib)...");
    int16_t state = radio->begin(868.0, 125.0, 9, 7, 0x12, 22, 8, 1.6);
    if (state != RADIOLIB_ERR_NONE) {
        ESP_LOGE(TAG, "LR2021 init failed: %d", state);
        while (true) { hal->delay(1000); }
    }
    ESP_LOGI(TAG, "LR2021 initialized OK");

    radio->setPacketSentAction(on_tx_done);

    ESP_LOGI(TAG, "Initializing BMP280...");
    bmp280_t bmp;
    memset(&bmp, 0, sizeof(bmp));
    bmp280_init(&bmp, I2C_NUM_0, 8, 9, 400000);

    ESP_LOGI(TAG, "Initializing power manager...");
    power_manager_init();

    telemetry_packet_t pkt;
    memset(&pkt, 0, sizeof(pkt));
    pkt.callsign_hash = 0x424C4E;

    int cycle = 0;
    while (1) {
        ESP_LOGI(TAG, "--- Cycle %d ---", cycle);

        float temp = 0, pressure = 0, altitude = 0;
        bmp280_read(&bmp, &temp, &pressure, &altitude);
        ESP_LOGI(TAG, "BMP280: %.1f C, %.1f hPa, %.0f m", temp, pressure, altitude);

        uint16_t cap_mv = power_manager_read_supercap_mv();
        ESP_LOGI(TAG, "Supercap: %d mV", cap_mv);

        telemetry_fill(&pkt, temp, pressure, altitude, cap_mv, cycle);

        uint8_t buf[TELEMETRY_SIZE];
        telemetry_serialize(&pkt, buf);

        ESP_LOGI(TAG, "TX %d bytes on 868 MHz...", TELEMETRY_SIZE);
        flag_tx_done = false;
        state = radio->startTransmit(buf, TELEMETRY_SIZE);
        if (state != RADIOLIB_ERR_NONE) {
            ESP_LOGE(TAG, "startTransmit failed: %d", state);
        } else {
            uint32_t timeout = 0;
            while (!flag_tx_done && timeout < 10000) {
                hal->delay(1);
                timeout++;
            }
            if (flag_tx_done) {
                ESP_LOGI(TAG, "TX complete");
            } else {
                ESP_LOGW(TAG, "TX timeout");
            }
        }

        radio->standby();

        cycle++;
        ESP_LOGI(TAG, "Sleeping 60s...");
        vTaskDelay(pdMS_TO_TICKS(60000));
    }
}
